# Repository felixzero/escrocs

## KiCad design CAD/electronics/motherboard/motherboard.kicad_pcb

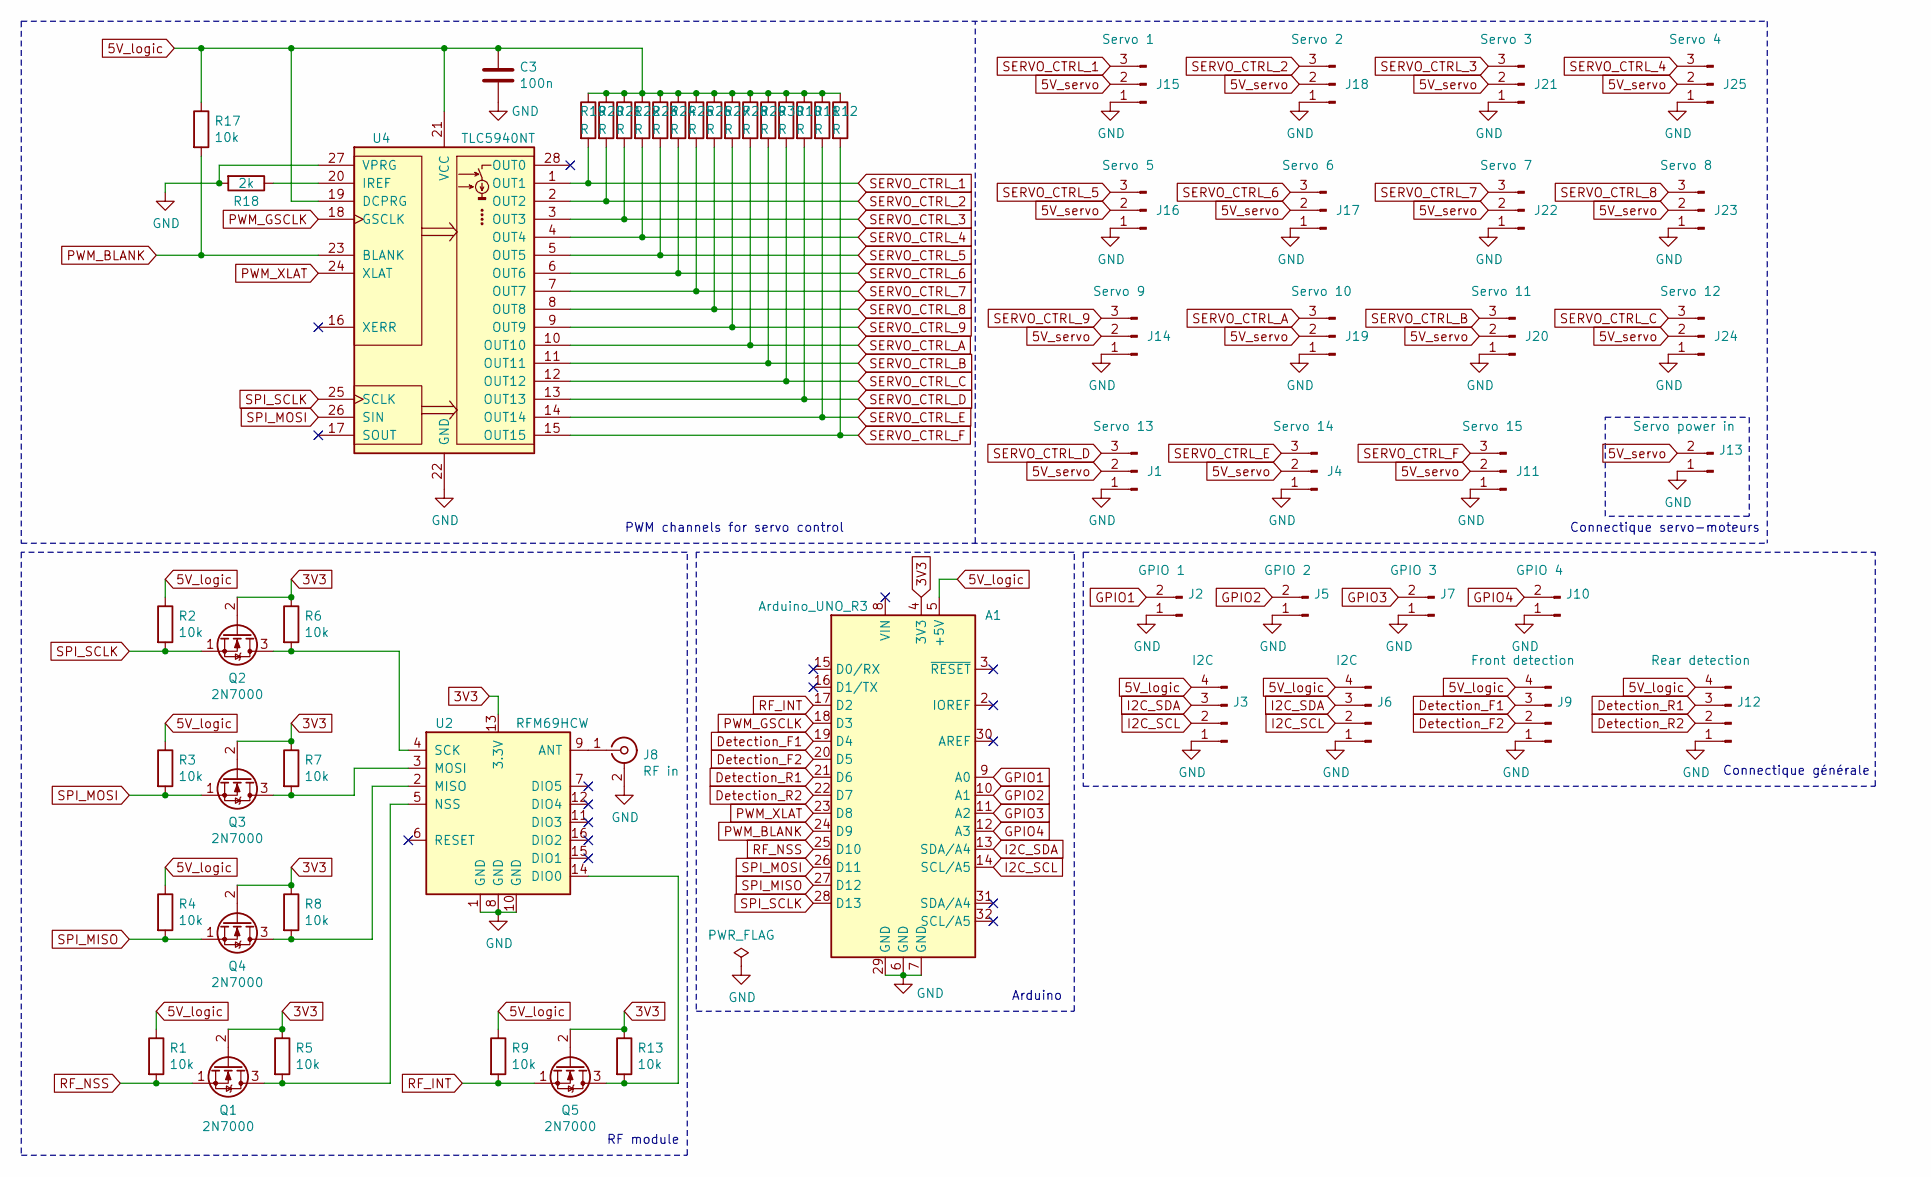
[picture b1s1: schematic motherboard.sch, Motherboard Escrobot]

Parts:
A1: Arduino_UNO_R3
C3: 100n; C_Axial_L5.1mm_D3.1mm_P10.00mm_Horizontal
J1: Servo 13; Molex_KK-254_AE-6410-03A_1x03_P2.54mm_Vertical
J2: GPIO 1; Molex_KK-254_AE-6410-02A_1x02_P2.54mm_Vertical
J3, J6: I2C; Molex_KK-254_AE-6410-04A_1x04_P2.54mm_Vertical
J4: Servo 14; Molex_KK-254_AE-6410-03A_1x03_P2.54mm_Vertical
J5: GPIO 2; Molex_KK-254_AE-6410-02A_1x02_P2.54mm_Vertical
J7: GPIO 3; Molex_KK-254_AE-6410-02A_1x02_P2.54mm_Vertical
J8: RF in; SMA_Samtec_SMA-J-P-X-ST-EM1_EdgeMount
J9: Front detection; Molex_KK-254_AE-6410-04A_1x04_P2.54mm_Vertical
J10: GPIO 4; Molex_KK-254_AE-6410-02A_1x02_P2.54mm_Vertical
J11: Servo 15; Molex_KK-254_AE-6410-03A_1x03_P2.54mm_Vertical
J12: Rear detection; Molex_KK-254_AE-6410-04A_1x04_P2.54mm_Vertical
J13: Servo power in; SolderWirePad_1x02_P5.08mm_Drill1.5mm
J14: Servo 9; Molex_KK-254_AE-6410-03A_1x03_P2.54mm_Vertical
J15: Servo 1; Molex_KK-254_AE-6410-03A_1x03_P2.54mm_Vertical
J16: Servo 5; Molex_KK-254_AE-6410-03A_1x03_P2.54mm_Vertical
J17: Servo 6; Molex_KK-254_AE-6410-03A_1x03_P2.54mm_Vertical
J18: Servo 2; Molex_KK-254_AE-6410-03A_1x03_P2.54mm_Vertical
J19: Servo 10; Molex_KK-254_AE-6410-03A_1x03_P2.54mm_Vertical
J20: Servo 11; Molex_KK-254_AE-6410-03A_1x03_P2.54mm_Vertical
J21: Servo 3; Molex_KK-254_AE-6410-03A_1x03_P2.54mm_Vertical
J22: Servo 7; Molex_KK-254_AE-6410-03A_1x03_P2.54mm_Vertical
J23: Servo 8; Molex_KK-254_AE-6410-03A_1x03_P2.54mm_Vertical
J24: Servo 12; Molex_KK-254_AE-6410-03A_1x03_P2.54mm_Vertical
J25: Servo 4; Molex_KK-254_AE-6410-03A_1x03_P2.54mm_Vertical
Q1, Q2, Q3, Q4, Q5: 2N7000; TO-92_Inline
R1, R2, R3, R4, R5, R6, R7, R8, R9, R13, R17: 10k; R_Axial_DIN0207_L6.3mm_D2.5mm_P2.54mm_Vertical
R10, R11, R12, R19, R20, R21, R22, R23, R24, R25, R26, R27, R28, R29, R30: R; R_Axial_DIN0207_L6.3mm_D2.5mm_P10.16mm_Horizontal
R18: 2k; R_Axial_DIN0207_L6.3mm_D2.5mm_P2.54mm_Vertical
U2: RFM69HCW; HOPERF_RFM9XW_SMD
U4: TLC5940NT; DIP-28_W7.62mm

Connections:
3V3: A1.4 (3V3), Q1.2 (G), Q2.2 (G), Q3.2 (G), Q4.2 (G), Q5.2 (G), R5.1, R6.1, R7.1, R8.1, R13.1, U2.13 (3.3V)
5V_logic: A1.5 (+5V), C3.1, J3.4, J6.4, J9.4, J12.4, R1.1, R2.1, R3.1, R4.1, R9.1, R10.1, R11.1, R12.1, R17.1, R19.1, R20.1, R21.1, R22.1, R23.1, R24.1, R25.1, R26.1, R27.1, R28.1, R29.1, R30.1, U4.19 (DCPRG), U4.21 (VCC)
5V_servo: J1.2, J4.2, J11.2, J13.2, J14.2, J15.2, J16.2, J17.2, J18.2, J19.2, J20.2, J21.2, J22.2, J23.2, J24.2, J25.2
Detection_F1: A1.19 (D4), J9.3
Detection_F2: A1.20 (D5), J9.2
Detection_R1: A1.21 (D6), J12.3
Detection_R2: A1.22 (D7), J12.2
GND: A1.6 (GND), A1.7 (GND), A1.29 (GND), C3.2, J1.1, J2.1, J3.1, J4.1, J5.1, J6.1, J7.1, J8.2 (Ext), J9.1, J10.1, J11.1, J12.1, J13.1, J14.1, J15.1, J16.1, J17.1, J18.1, J19.1, J20.1, J21.1, J22.1, J23.1, J24.1, J25.1, R18.2, U2.1 (GND), U2.8 (GND), U2.10 (GND), U4.22 (GND), U4.27 (VPRG)
GPIO1: A1.9 (A0), J2.2
GPIO2: A1.10 (A1), J5.2
GPIO3: A1.11 (A2), J7.2
GPIO4: A1.12 (A3), J10.2
I2C_SCL: A1.14 (SCL/A5), J3.2, J6.2
I2C_SDA: A1.13 (SDA/A4), J3.3, J6.3
unnamed: J8.1 (In), U2.9 (ANT)
unnamed: Q1.3 (D), R5.2, U2.5 (NSS)
unnamed: Q2.3 (D), R6.2, U2.4 (SCK)
unnamed: Q3.3 (D), R7.2, U2.3 (MOSI)
unnamed: Q4.3 (D), R8.2, U2.2 (MISO)
unnamed: Q5.3 (D), R13.2, U2.14 (DIO0)
unnamed: R18.1, U4.20 (IREF)
PWM_BLANK: A1.24 (D9), R17.2, U4.23 (BLANK)
PWM_GSCLK: A1.18 (D3), U4.18 (GSCLK)
PWM_XLAT: A1.23 (D8), U4.24 (XLAT)
RF_INT: A1.17 (D2), Q5.1 (S), R9.2
RF_NSS: A1.25 (D10), Q1.1 (S), R1.2
SERVO_CTRL_1: J15.3, R19.2, U4.1 (OUT1)
SERVO_CTRL_2: J18.3, R20.2, U4.2 (OUT2)
SERVO_CTRL_3: J21.3, R21.2, U4.3 (OUT3)
SERVO_CTRL_4: J25.3, R22.2, U4.4 (OUT4)
SERVO_CTRL_5: J16.3, R23.2, U4.5 (OUT5)
SERVO_CTRL_6: J17.3, R24.2, U4.6 (OUT6)
SERVO_CTRL_7: J22.3, R25.2, U4.7 (OUT7)
SERVO_CTRL_8: J23.3, R26.2, U4.8 (OUT8)
SERVO_CTRL_9: J14.3, R27.2, U4.9 (OUT9)
SERVO_CTRL_A: J19.3, R28.2, U4.10 (OUT10)
SERVO_CTRL_B: J20.3, R29.2, U4.11 (OUT11)
SERVO_CTRL_C: J24.3, R30.2, U4.12 (OUT12)
SERVO_CTRL_D: J1.3, R10.2, U4.13 (OUT13)
SERVO_CTRL_E: J4.3, R11.2, U4.14 (OUT14)
SERVO_CTRL_F: J11.3, R12.2, U4.15 (OUT15)
SPI_MISO: A1.27 (D12), Q4.1 (S), R4.2
SPI_MOSI: A1.26 (D11), Q3.1 (S), R3.2, U4.26 (SIN)
SPI_SCLK: A1.28 (D13), Q2.1 (S), R2.2, U4.25 (SCLK)

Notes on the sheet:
PWM channels for servo control
Connectique servo-moteurs
Arduino
Connectique générale
RF module

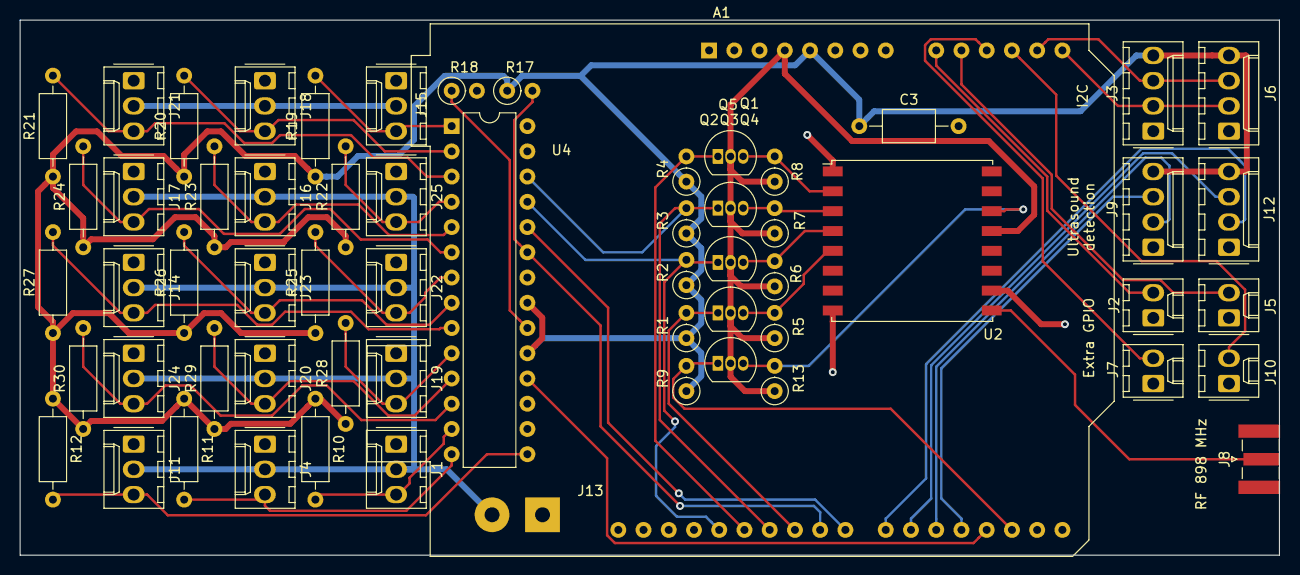
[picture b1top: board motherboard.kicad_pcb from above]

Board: 2 copper layers, 126.7 x 53.8 mm, 61 parts (0 on the bottom side), 44 nets.

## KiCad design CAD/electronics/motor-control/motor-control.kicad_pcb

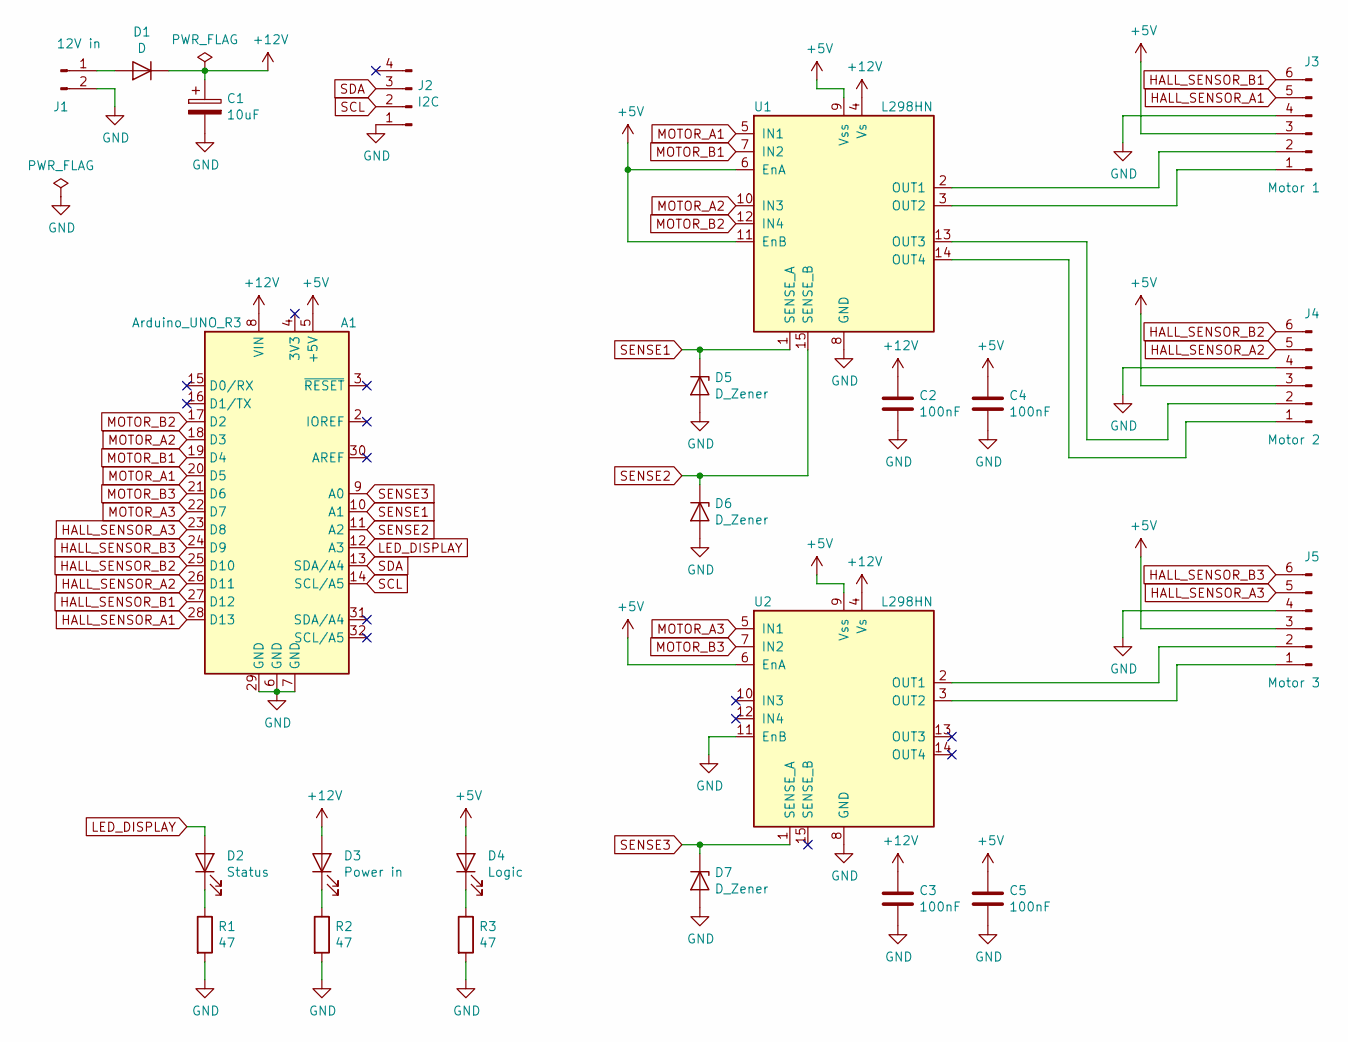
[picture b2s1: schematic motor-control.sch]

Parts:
A1: Arduino_UNO_R3
C1: 10uF; CP_Radial_D5.0mm_P2.00mm
C2, C3, C4, C5: 100nF; C_Disc_D4.3mm_W1.9mm_P5.00mm
D1: D; D_DO-201AE_P12.70mm_Horizontal
D2: Status; LED_D3.0mm_Clear
D3: Power in; LED_D3.0mm_Clear
D4: Logic; LED_D3.0mm_Clear
D5, D6, D7: D_Zener; D_DO-35_SOD27_P10.16mm_Horizontal
J1: 12V in; SolderWirePad_1x02_P5.08mm_Drill1.5mm
J2: I2C; Molex_KK-254_AE-6410-04A_1x04_P2.54mm_Vertical
J3: Motor 1; JST_PH_S6B-PH-K_1x06_P2.00mm_Horizontal
J4: Motor 2; JST_PH_S6B-PH-K_1x06_P2.00mm_Horizontal
J5: Motor 3; JST_PH_S6B-PH-K_1x06_P2.00mm_Horizontal
R1, R2, R3: 47; R_Axial_DIN0207_L6.3mm_D2.5mm_P10.16mm_Horizontal
U1, U2: L298HN; TO-220-15_P2.54x2.54mm_StaggerOdd_Lead4.58mm_Vertical

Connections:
+5V: A1.5 (+5V), C4.1, C5.1, D4.2 (A), J3.3, J4.3, J5.3, U1.6 (EnA), U1.9 (Vss), U1.11 (EnB), U2.6 (EnA), U2.9 (Vss)
+12V: A1.8 (VIN), C1.1, C2.1, C3.1, D1.1 (K), D3.2 (A), U1.4 (Vs), U2.4 (Vs)
GND: A1.6 (GND), A1.7 (GND), A1.29 (GND), C1.2, C2.2, C3.2, C4.2, C5.2, D5.2 (A), D6.2 (A), D7.2 (A), J1.2, J2.1, J3.4, J4.4, J5.4, R1.2, R2.2, R3.2, U1.8 (GND), U2.8 (GND), U2.11 (EnB)
HALL_SENSOR_A1: A1.28 (D13), J3.5
HALL_SENSOR_A2: A1.26 (D11), J4.5
HALL_SENSOR_A3: A1.23 (D8), J5.5
HALL_SENSOR_B1: A1.27 (D12), J3.6
HALL_SENSOR_B2: A1.25 (D10), J4.6
HALL_SENSOR_B3: A1.24 (D9), J5.6
LED_DISPLAY: A1.12 (A3), D2.2 (A)
MOTOR_A1: A1.20 (D5), U1.5 (IN1)
MOTOR_A2: A1.18 (D3), U1.10 (IN3)
MOTOR_A3: A1.22 (D7), U2.5 (IN1)
MOTOR_B1: A1.19 (D4), U1.7 (IN2)
MOTOR_B2: A1.17 (D2), U1.12 (IN4)
MOTOR_B3: A1.21 (D6), U2.7 (IN2)
unnamed: D1.2 (A), J1.1
unnamed: D2.1 (K), R1.1
unnamed: D3.1 (K), R2.1
unnamed: D4.1 (K), R3.1
unnamed: J3.1, U1.3 (OUT2)
unnamed: J3.2, U1.2 (OUT1)
unnamed: J4.1, U1.14 (OUT4)
unnamed: J4.2, U1.13 (OUT3)
unnamed: J5.1, U2.3 (OUT2)
unnamed: J5.2, U2.2 (OUT1)
SCL: A1.14 (SCL/A5), J2.2
SDA: A1.13 (SDA/A4), J2.3
SENSE1: A1.10 (A1), D5.1 (K), U1.1 (SENSE_A)
SENSE2: A1.11 (A2), D6.1 (K), U1.15 (SENSE_B)
SENSE3: A1.9 (A0), D7.1 (K), U2.1 (SENSE_A)

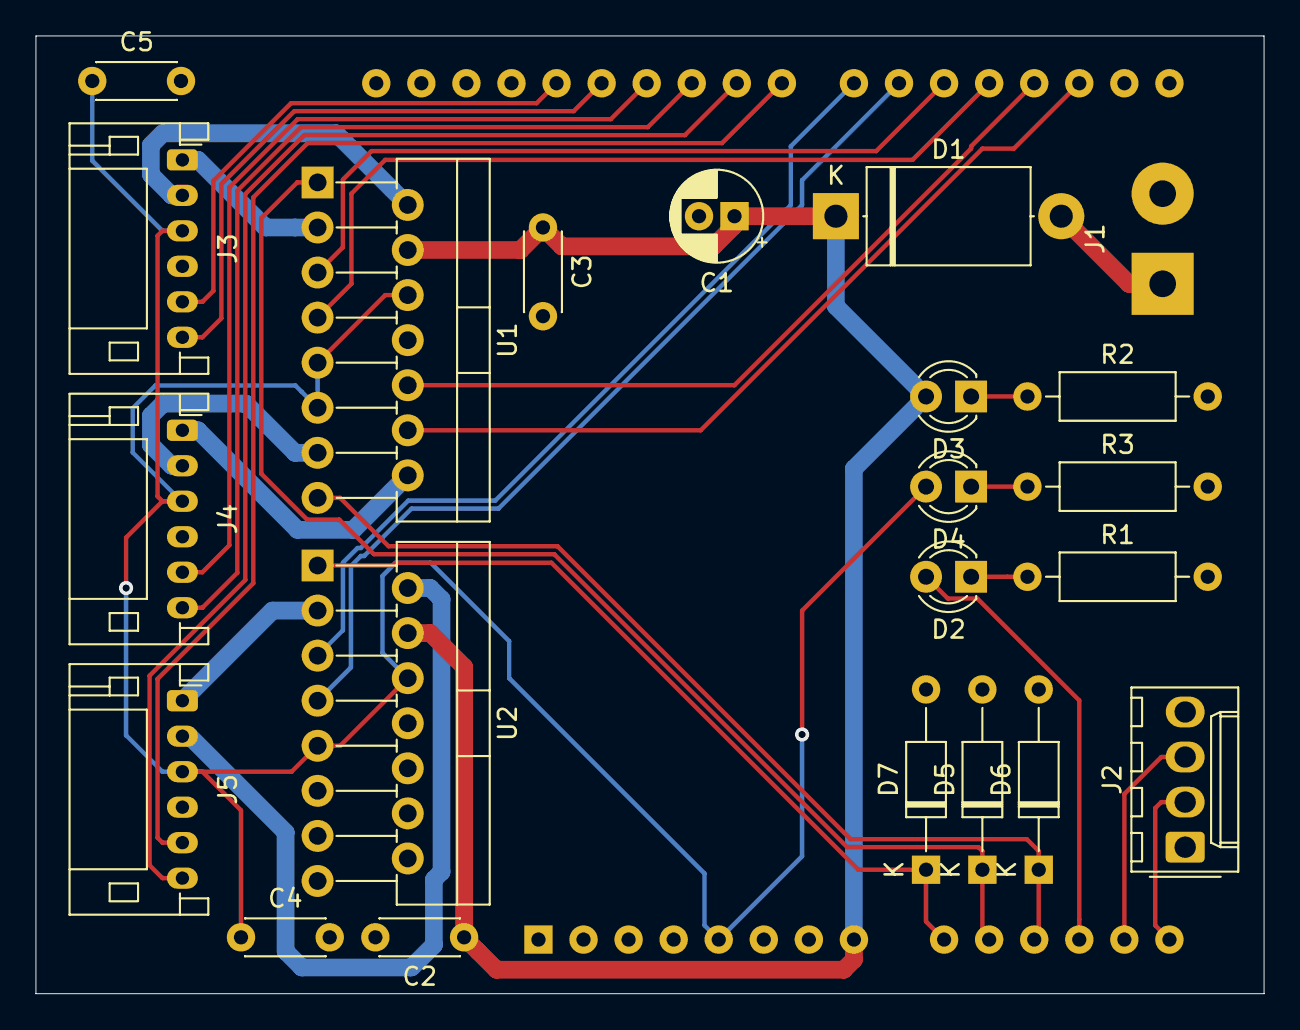
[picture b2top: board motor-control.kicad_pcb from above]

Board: 2 copper layers, 69.2 x 54.0 mm, 23 parts (1 on the bottom side), 31 nets.

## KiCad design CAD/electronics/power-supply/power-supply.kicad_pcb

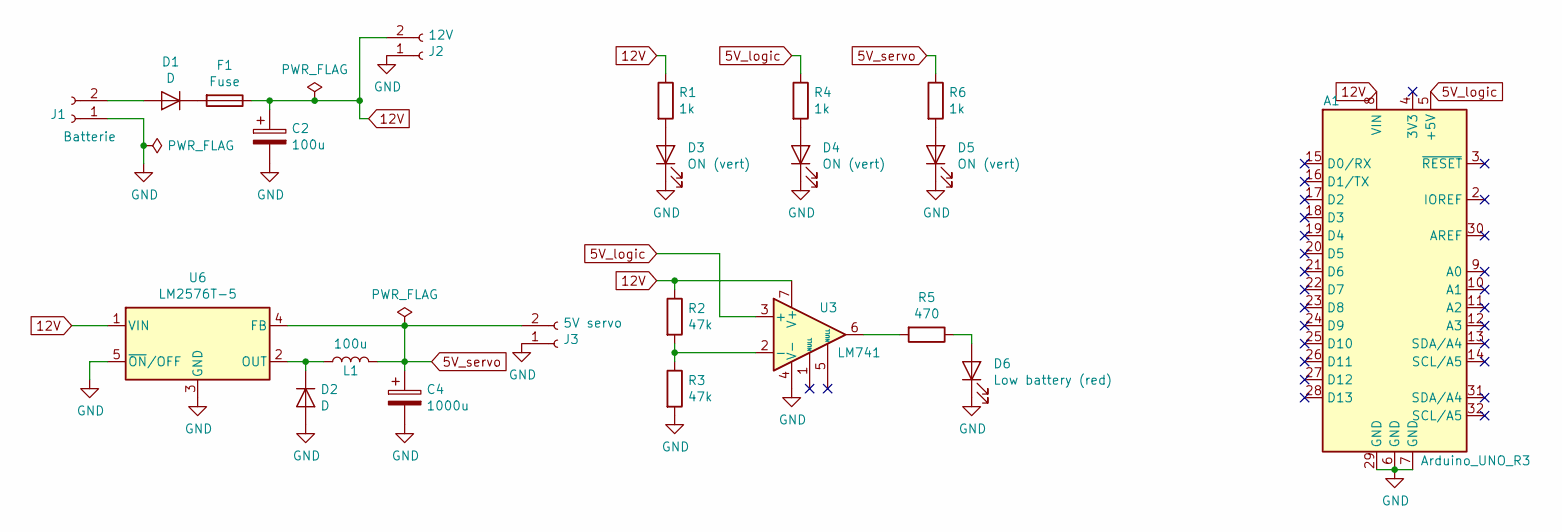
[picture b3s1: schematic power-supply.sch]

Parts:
A1: Arduino_UNO_R3
C2: 100u; CP_Radial_D6.3mm_P2.50mm
C4: 1000u; CP_Radial_D10.0mm_P5.00mm
D1, D2: D; D_P600_R-6_P12.70mm_Horizontal
D3, D4, D5: ON (vert); LED_D1.8mm_W3.3mm_H2.4mm
D6: Low battery (red); LED_D1.8mm_W3.3mm_H2.4mm
F1: Fuse; Fuseholder_Cylinder-5x20mm_Stelvio-Kontek_PTF78_Horizontal_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
J1: Batterie; SolderWirePad_1x02_P5.08mm_Drill1.5mm
J2: 12V; SolderWirePad_1x02_P5.08mm_Drill1.5mm
J3: 5V servo; SolderWirePad_1x02_P5.08mm_Drill1.5mm
L1: 100u; L_Toroid_Vertical_L54.0mm_W23.8mm_P20.10mm_Bourns_5700
R1, R4, R6: 1k; R_Axial_DIN0207_L6.3mm_D2.5mm_P7.62mm_Horizontal
R2, R3: 47k; R_Axial_DIN0204_L3.6mm_D1.6mm_P7.62mm_Horizontal
R5: 470; R_Axial_DIN0207_L6.3mm_D2.5mm_P7.62mm_Horizontal
U3: LM741; DIP-8_W7.62mm
U6: LM2576T-5; TO-220-5_Vertical

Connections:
5V_logic: A1.5 (+5V), R4.1, U3.3 (+)
5V_servo: C4.1, J3.2, L1.2, R6.1, U6.4 (FB)
12V: A1.8 (VIN), C2.1, F1.1, J2.2, R1.1, R2.1, U3.7 (V+), U6.1 (VIN)
GND: A1.6 (GND), A1.7 (GND), A1.29 (GND), C2.2, C4.2, D2.2 (A), D3.1 (K), D4.1 (K), D5.1 (K), D6.1 (K), J1.1, J2.1, J3.1, R3.2, U3.4 (V-), U6.3 (GND), U6.5 (~ON~/OFF)
unnamed: D1.1 (K), F1.2
unnamed: D1.2 (A), J1.2
unnamed: D2.1 (K), L1.1, U6.2 (OUT)
unnamed: D3.2 (A), R1.2
unnamed: D4.2 (A), R4.2
unnamed: D5.2 (A), R6.2
unnamed: D6.2 (A), R5.1
unnamed: R2.2, R3.1, U3.2 (-)
unnamed: R5.2, U3.6

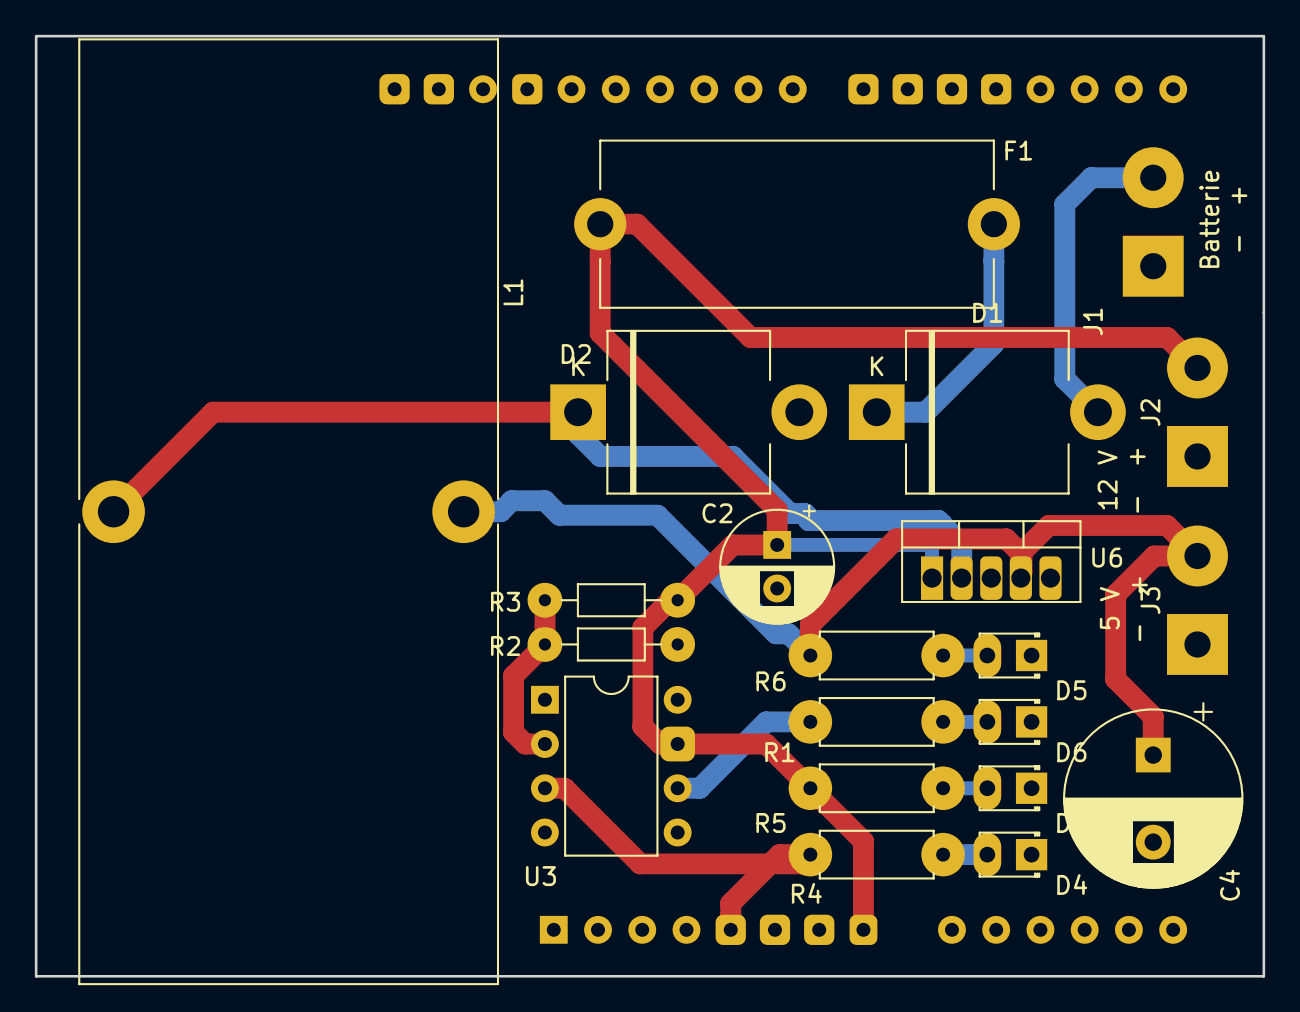
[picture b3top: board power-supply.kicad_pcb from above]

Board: 2 copper layers, 70.5 x 54.0 mm, 22 parts (1 on the bottom side), 13 nets.

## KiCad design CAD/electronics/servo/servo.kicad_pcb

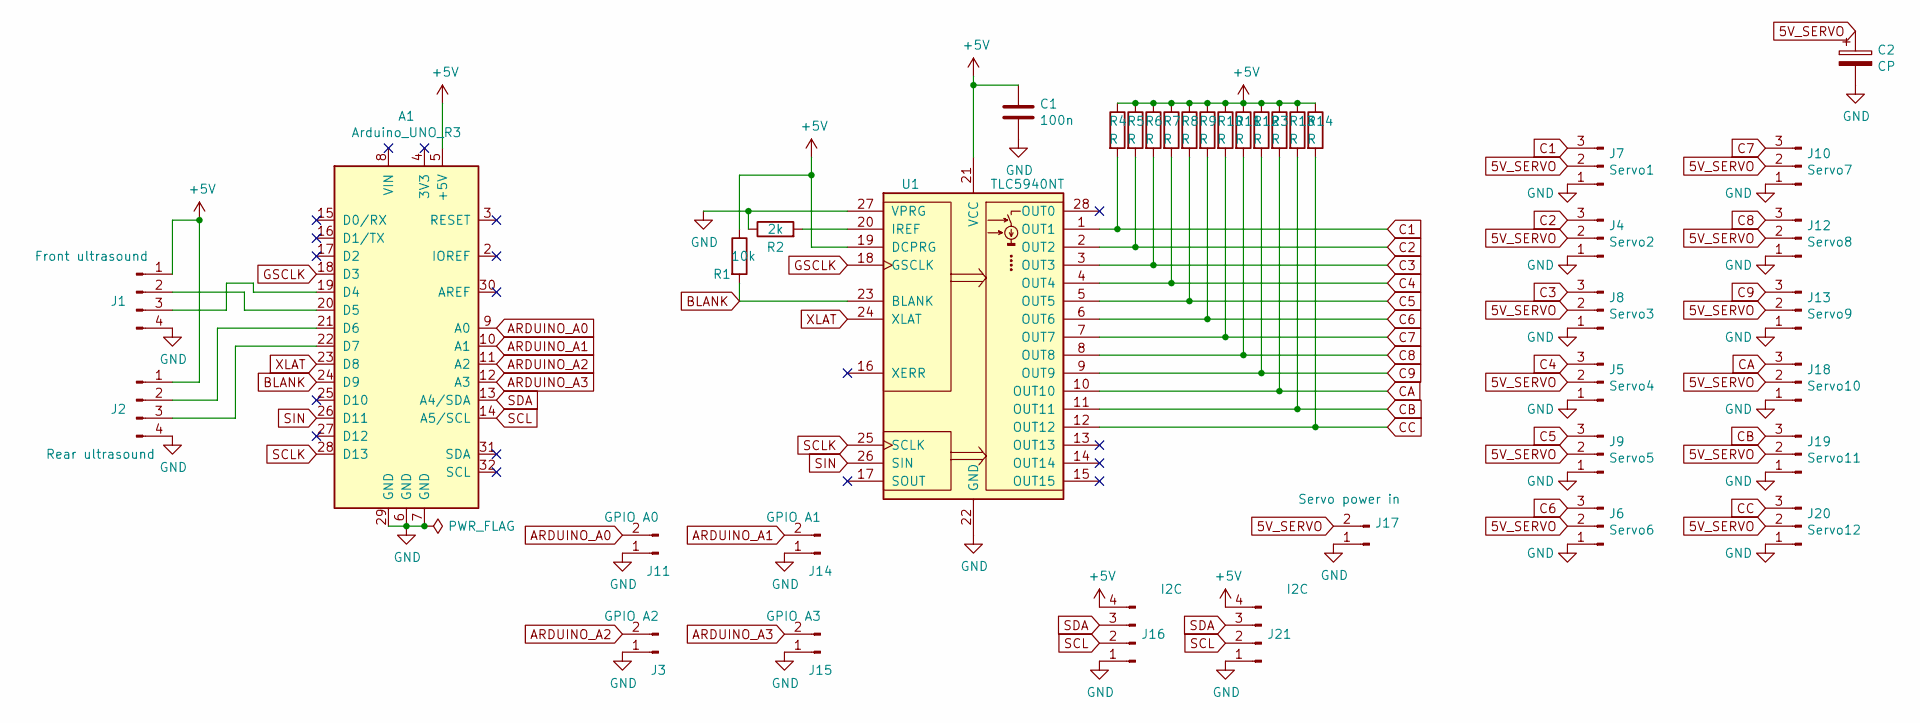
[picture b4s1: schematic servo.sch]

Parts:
A1: Arduino_UNO_R3
C1: 100n; C_Disc_D7.5mm_W5.0mm_P10.00mm
C2: CP; CP_Radial_D8.0mm_P5.00mm
J1: Front ultrasound; Molex_KK-254_AE-6410-04A_1x04_P2.54mm_Vertical
J2: Rear ultrasound; Molex_KK-254_AE-6410-04A_1x04_P2.54mm_Vertical
J3: GPIO A2; Molex_KK-254_AE-6410-02A_1x02_P2.54mm_Vertical
J4: Servo2; Molex_KK-254_AE-6410-03A_1x03_P2.54mm_Vertical
J5: Servo4; Molex_KK-254_AE-6410-03A_1x03_P2.54mm_Vertical
J6: Servo6; Molex_KK-254_AE-6410-03A_1x03_P2.54mm_Vertical
J7: Servo1; Molex_KK-254_AE-6410-03A_1x03_P2.54mm_Vertical
J8: Servo3; Molex_KK-254_AE-6410-03A_1x03_P2.54mm_Vertical
J9: Servo5; Molex_KK-254_AE-6410-03A_1x03_P2.54mm_Vertical
J10: Servo7; Molex_KK-254_AE-6410-03A_1x03_P2.54mm_Vertical
J11: GPIO A0; Molex_KK-254_AE-6410-02A_1x02_P2.54mm_Vertical
J12: Servo8; Molex_KK-254_AE-6410-03A_1x03_P2.54mm_Vertical
J13: Servo9; Molex_KK-254_AE-6410-03A_1x03_P2.54mm_Vertical
J14: GPIO A1; Molex_KK-254_AE-6410-02A_1x02_P2.54mm_Vertical
J15: GPIO A3; Molex_KK-254_AE-6410-02A_1x02_P2.54mm_Vertical
J16, J21: I2C; Molex_KK-254_AE-6410-04A_1x04_P2.54mm_Vertical
J17: Servo power in; PinSocket_1x02_P2.54mm_Vertical
J18: Servo10; Molex_KK-254_AE-6410-03A_1x03_P2.54mm_Vertical
J19: Servo11; Molex_KK-254_AE-6410-03A_1x03_P2.54mm_Vertical
J20: Servo12; Molex_KK-254_AE-6410-03A_1x03_P2.54mm_Vertical
R1: 10k; R_Axial_DIN0207_L6.3mm_D2.5mm_P7.62mm_Horizontal
R2: 2k; R_Axial_DIN0207_L6.3mm_D2.5mm_P7.62mm_Horizontal
R3, R4, R5, R6, R7, R8, R9, R10, R11, R12, R13, R14: R; R_Axial_DIN0204_L3.6mm_D1.6mm_P7.62mm_Horizontal
U1: TLC5940NT; DIP-28_W7.62mm

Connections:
5V_SERVO: C2.1, J4.2, J5.2, J6.2, J7.2, J8.2, J9.2, J10.2, J12.2, J13.2, J17.2, J18.2, J19.2, J20.2
+5V: A1.5 (+5V), C1.1, J1.1, J2.1, J16.4, J21.4, R1.1, R3.1, R4.1, R5.1, R6.1, R7.1, R8.1, R9.1, R10.1, R11.1, R12.1, R13.1, R14.1, U1.19 (DCPRG), U1.21 (VCC)
ARDUINO_A0: A1.9 (A0), J11.2
ARDUINO_A1: A1.10 (A1), J14.2
ARDUINO_A2: A1.11 (A2), J3.2
ARDUINO_A3: A1.12 (A3), J15.2
BLANK: A1.24 (D9), R1.2, U1.23 (BLANK)
C1: J7.3, R4.2, U1.1 (OUT1)
C2: J4.3, R5.2, U1.2 (OUT2)
C3: J8.3, R6.2, U1.3 (OUT3)
C4: J5.3, R7.2, U1.4 (OUT4)
C5: J9.3, R8.2, U1.5 (OUT5)
C6: J6.3, R9.2, U1.6 (OUT6)
C7: J10.3, R10.2, U1.7 (OUT7)
C8: J12.3, R11.2, U1.8 (OUT8)
C9: J13.3, R12.2, U1.9 (OUT9)
CA: J18.3, R3.2, U1.10 (OUT10)
CB: J19.3, R13.2, U1.11 (OUT11)
CC: J20.3, R14.2, U1.12 (OUT12)
GND: A1.6 (GND), A1.7 (GND), A1.29 (GND), C1.2, C2.2, J1.4, J2.4, J3.1, J4.1, J5.1, J6.1, J7.1, J8.1, J9.1, J10.1, J11.1, J12.1, J13.1, J14.1, J15.1, J16.1, J17.1, J18.1, J19.1, J20.1, J21.1, R2.1, U1.22 (GND), U1.27 (VPRG)
GSCLK: A1.18 (D3), U1.18 (GSCLK)
unnamed: A1.19 (D4), J1.3
unnamed: A1.20 (D5), J1.2
unnamed: A1.21 (D6), J2.2
unnamed: A1.22 (D7), J2.3
unnamed: R2.2, U1.20 (IREF)
SCL: A1.14 (A5/SCL), J16.2, J21.2
SCLK: A1.28 (D13), U1.25 (SCLK)
SDA: A1.13 (A4/SDA), J16.3, J21.3
SIN: A1.26 (D11), U1.26 (SIN)
XLAT: A1.23 (D8), U1.24 (XLAT)

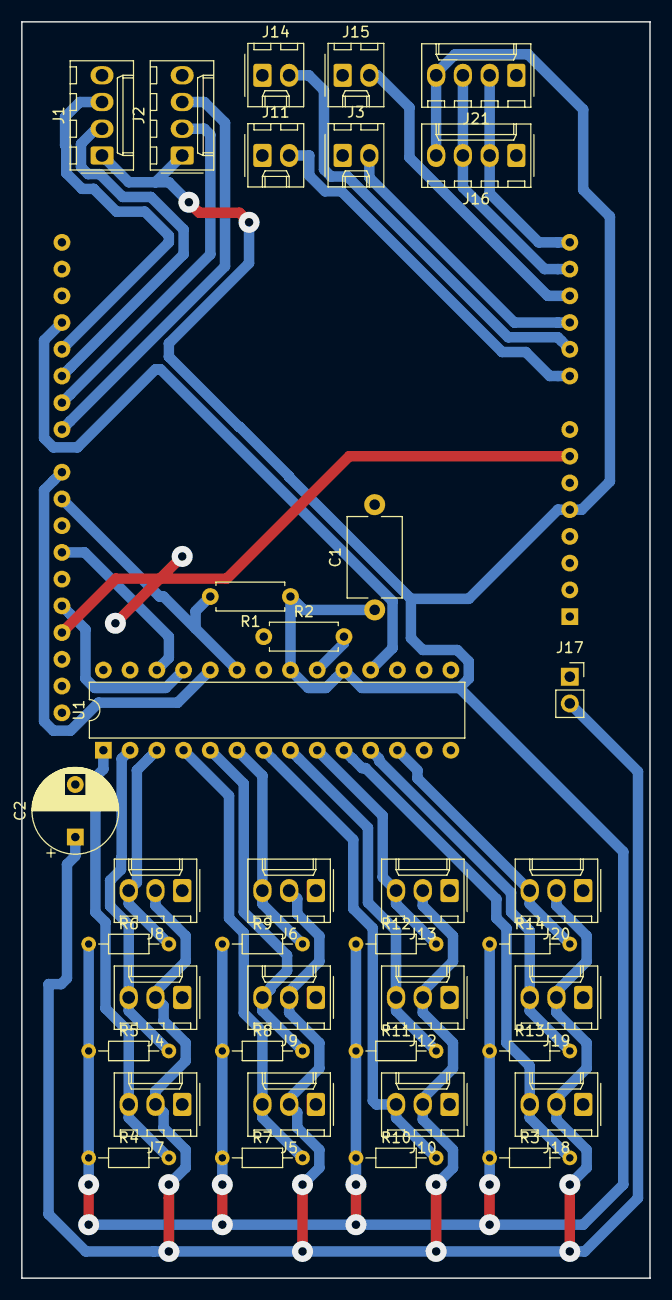
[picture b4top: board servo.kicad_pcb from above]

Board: 2 copper layers, 59.7 x 119.4 mm, 39 parts (1 on the bottom side), 31 nets.

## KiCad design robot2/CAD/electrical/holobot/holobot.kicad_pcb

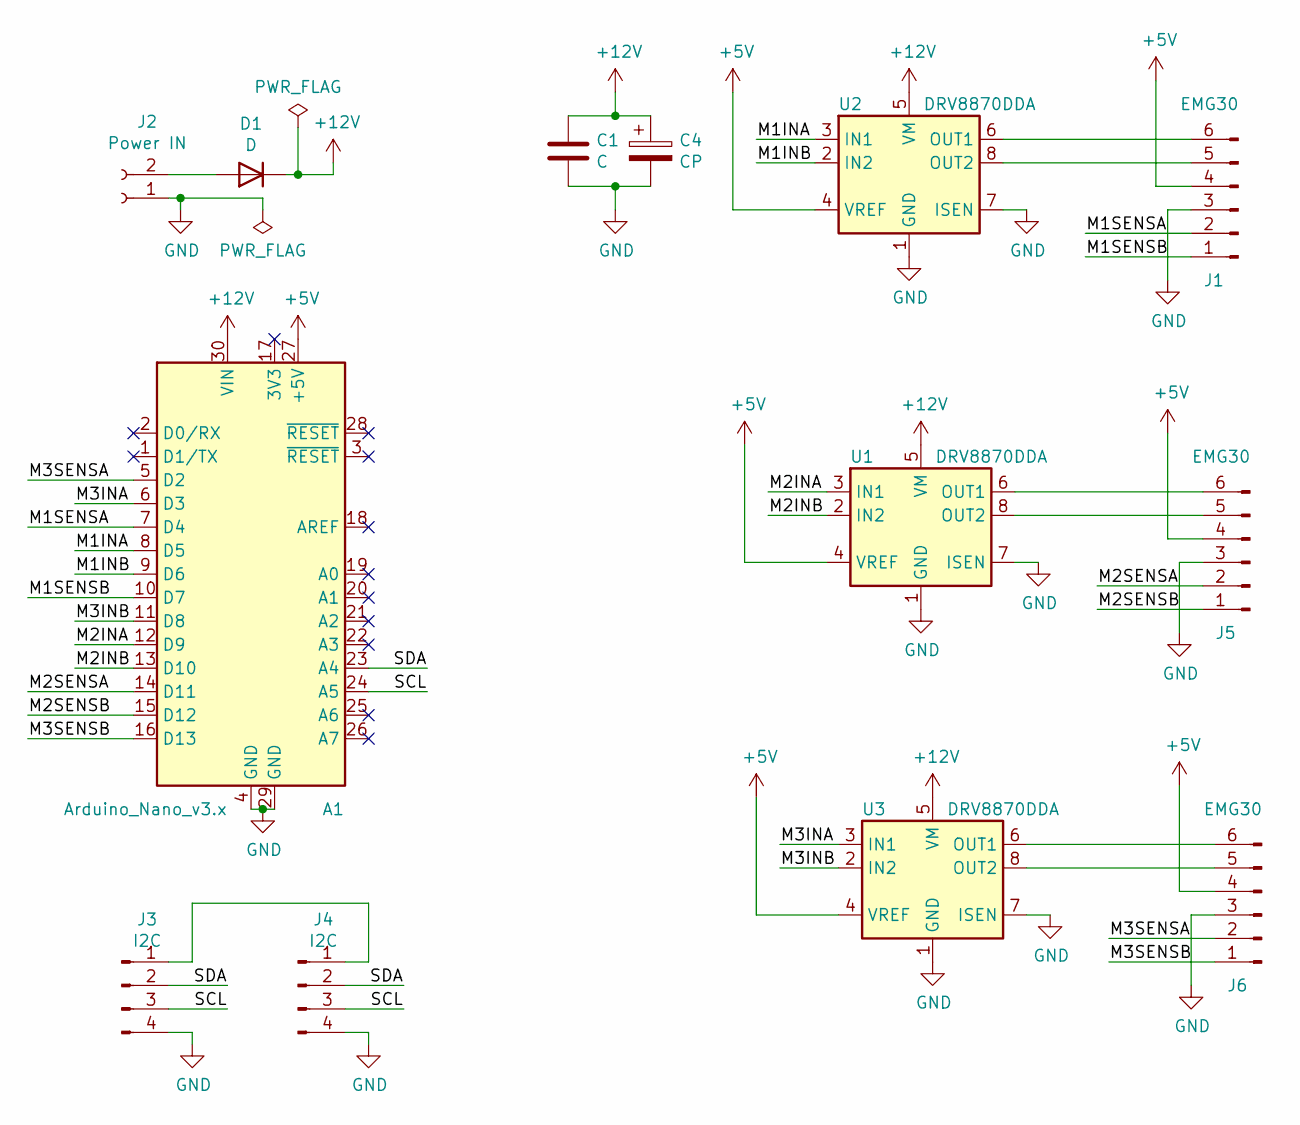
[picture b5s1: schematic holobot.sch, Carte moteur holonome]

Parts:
A1: Arduino_Nano_v3.x; Arduino_Nano
C1: C; C_Rect_L4.6mm_W3.0mm_P2.50mm_MKS02_FKP02
C4: CP; CP_Radial_D7.5mm_P2.50mm
D1: D; D_DO-201_P12.70mm_Horizontal
J1, J5, J6: EMG30; JST_PH_S6B-PH-K_1x06_P2.00mm_Horizontal
J2: Power IN; PinHeader_1x02_P2.54mm_Vertical
J3, J4: I2C; PinHeader_1x04_P2.54mm_Vertical
U1, U2, U3: DRV8870DDA; Texas_HTSOP-8-1EP_3.9x4.9mm_P1.27mm_EP2.95x4.9mm_Mask2.4x3.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

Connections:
+5V: A1.27 (+5V), J1.4, J5.4, J6.4, U1.4 (VREF), U2.4 (VREF), U3.4 (VREF)
+12V: A1.30 (VIN), C1.1, C4.1, D1.1 (K), U1.5 (VM), U2.5 (VM), U3.5 (VM)
/M1INA: A1.8 (D5), U2.3 (IN1)
/M1INB: A1.9 (D6), U2.2 (IN2)
/M1SENSA: A1.7 (D4), J1.2
/M1SENSB: A1.10 (D7), J1.1
/M2INA: A1.12 (D9), U1.3 (IN1)
/M2INB: A1.13 (D10), U1.2 (IN2)
/M2SENSA: A1.14 (D11), J5.2
/M2SENSB: A1.15 (D12), J5.1
/M3INA: A1.6 (D3), U3.3 (IN1)
/M3INB: A1.11 (D8), U3.2 (IN2)
/M3SENSA: A1.5 (D2), J6.2
/M3SENSB: A1.16 (D13), J6.1
/SCL: A1.24 (A5), J3.3, J4.3
/SDA: A1.23 (A4), J3.2, J4.2
GND: A1.4 (GND), A1.29 (GND), C1.2, C4.2, J1.3, J2.1, J3.4, J4.4, J5.3, J6.3, U1.1 (GND), U1.7 (ISEN), U1.9 (GND), U2.1 (GND), U2.7 (ISEN), U2.9 (GND), U3.1 (GND), U3.7 (ISEN), U3.9 (GND)
unnamed: D1.2 (A), J2.2
unnamed: J1.5, U2.8 (OUT2)
unnamed: J1.6, U2.6 (OUT1)
unnamed: J3.1, J4.1
unnamed: J5.5, U1.8 (OUT2)
unnamed: J5.6, U1.6 (OUT1)
unnamed: J6.5, U3.8 (OUT2)
unnamed: J6.6, U3.6 (OUT1)

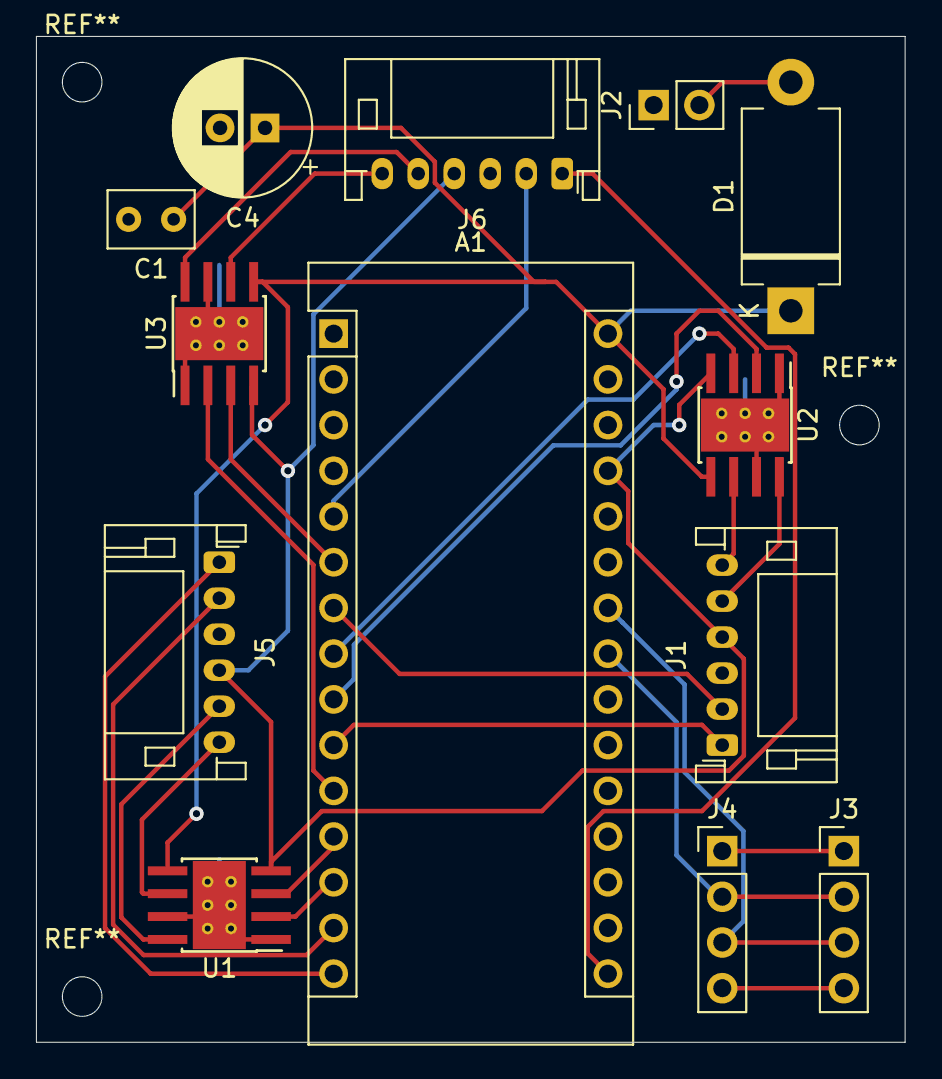
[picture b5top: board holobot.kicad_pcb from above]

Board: 2 copper layers, 48.3 x 55.9 mm, 13 parts (0 on the bottom side), 25 nets.

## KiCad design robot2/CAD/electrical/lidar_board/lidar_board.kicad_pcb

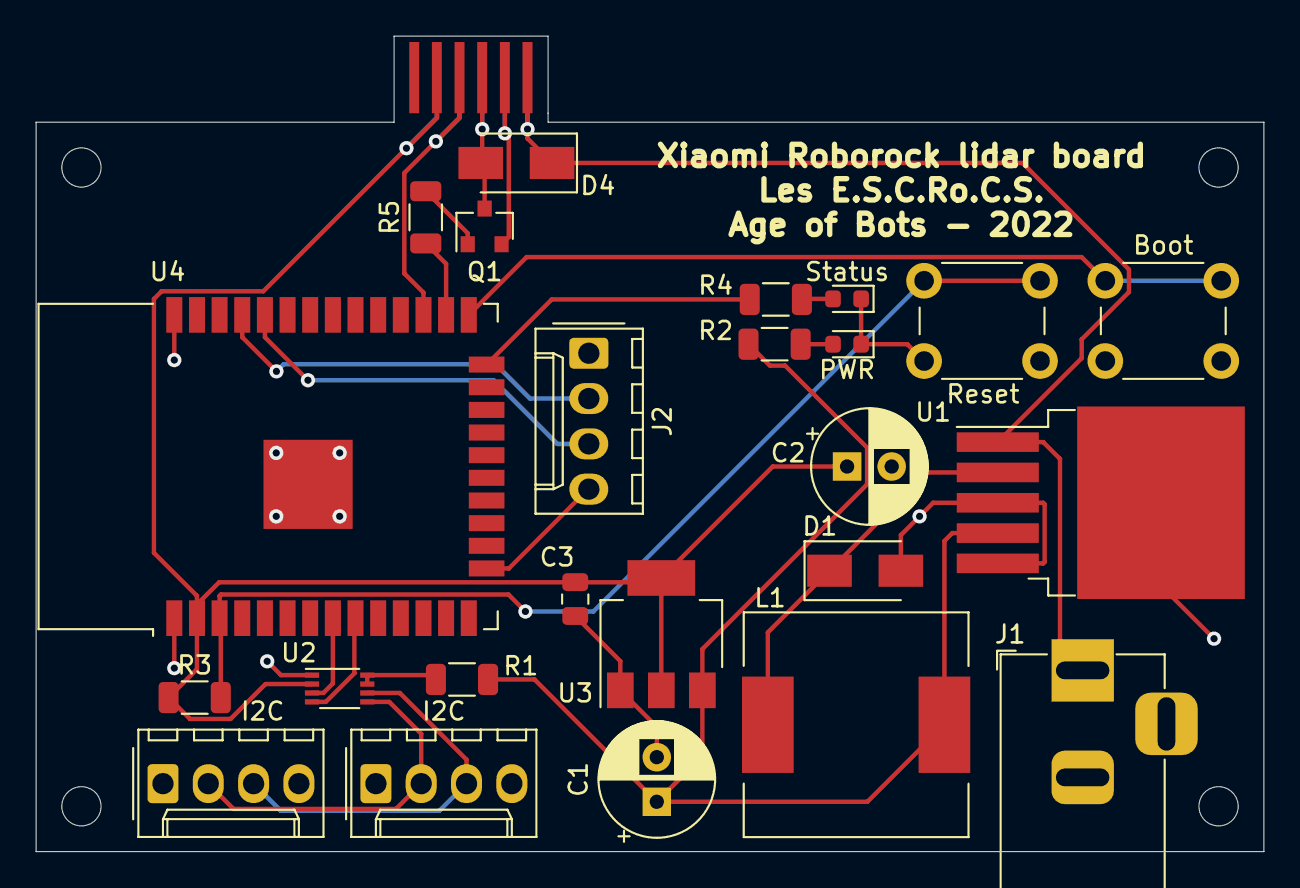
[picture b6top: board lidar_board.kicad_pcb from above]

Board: 2 copper layers, 68.8 x 45.7 mm, 25 parts (0 on the bottom side), 21 nets.

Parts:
Boot: Boot; SW_PUSH_6mm
C1, C2: 10u; CP_Radial_D6.3mm_P2.50mm
C3: 100n; C_0805_2012Metric
D1, D4: SS54; D_SMA
I2C, I2C#2: I2C bus; Molex_KK-254_AE-6410-04A_1x04_P2.54mm_Vertical
J1: 12V in; BarrelJack_Horizontal
J2: UART; Molex_KK-254_AE-6410-04A_1x04_P2.54mm_Vertical
J5: Lidar connector; Roborock lidar connector
L1: 100u; L_12x12mm_H6mm
PWR: PWR; LED_0603_1608Metric
Q1: AO3400A; SOT-23
R1: 100k; R_1206_3216Metric
R2, R4: 100; R_1206_3216Metric
R3: 10k; R_1206_3216Metric
R5: 470; R_1206_3216Metric
Reset: Reset; SW_PUSH_6mm
Status: Status; LED_0603_1608Metric
U1: LM2576HVS-5; TO-263-5_TabPin3
U2: PCA9306DC1; VSSOP-8_2.3x2mm_P0.5mm
U3: AMS1117-3.3; SOT-223-3_TabPin2
U4: ESP32-WROOM-32

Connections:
+3V3: C2.1, C3.1, J5.9, J5.10, R3.1, U2.2, U3.2, U4.2
+5V: C1.1, L1.2, R1.1, R2.1, U1.4, U3.3
+12V: D4.1, J1.1, J5.1, J5.2, U1.1
/I2C_SCL: U2.3, U4.8
/I2C_SDA: U2.4, U4.9
/LDS_TX: J5.7, J5.8, U4.27
/MOT-: D4.2, J5.5, J5.6, Q1.3
/MOT_PWM: R5.2, U4.26
/UART_MISO: J2.2, U4.35
/UART_MOSI: J2.3, U4.34
GND: Boot.2, C1.2, C2.2, C3.2, D1.2, I2C.4, I2C#2.4, J1.2, J2.4, J5.3, J5.4, PWR.1, Q1.2, Reset.2, Status.1, U1.3, U1.5, U2.1, U3.1, U4.1, U4.15, U4.38, U4.39
unnamed: D1.1, L1.1, U1.2
unnamed: PWR.2, R2.2
unnamed: R4.2, Status.2
unnamed: I2C.2, I2C#2.2, U2.5
unnamed: I2C.3, I2C#2.3, U2.6
unnamed: Q1.1, R5.1
unnamed: R1.2, U2.7, U2.8
unnamed: R3.2, Reset.1, U4.3
unnamed: R4.1, U4.24
unnamed: Boot.1, U4.25
